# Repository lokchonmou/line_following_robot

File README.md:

line_following_robot
====================

line following robot with Arduino, using DFduino UNO, dfrobot motor, home_made IR sensor to track line

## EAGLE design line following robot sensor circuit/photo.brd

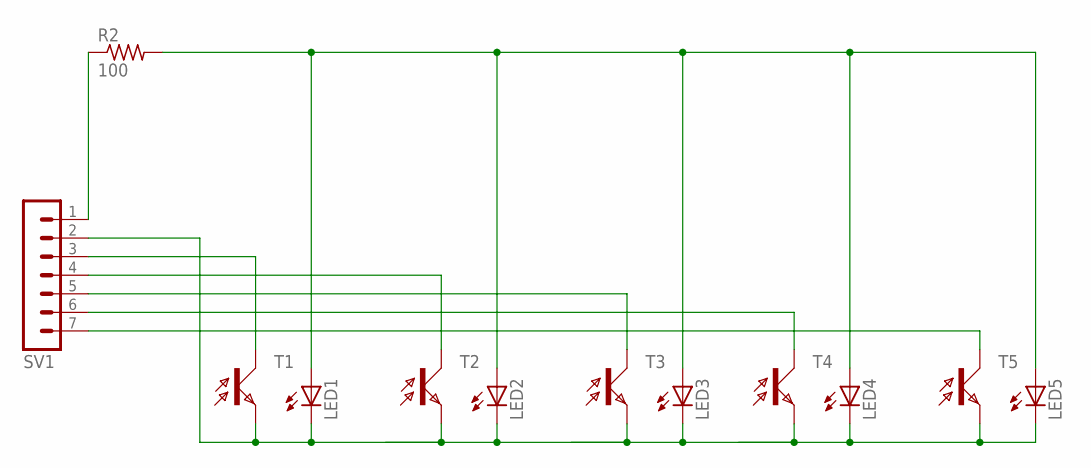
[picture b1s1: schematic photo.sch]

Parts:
LED1, LED2, LED3, LED4, LED5: LED3MM
R2: 100; 0204/7
SV1: MA07-1
T1, T2, T3, T4, T5: LPT80A

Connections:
unnamed: LED1.A, LED2.A, LED3.A, LED4.A, LED5.A, R2.2
unnamed: SV1.4, T2.C
unnamed: R2.1, SV1.1
unnamed: SV1.3, T1.C
unnamed: SV1.5, T3.C
unnamed: SV1.6, T4.C
unnamed: LED1.K (C), LED2.K (C), LED3.K (C), LED4.K (C), LED5.K (C), SV1.2, T1.E, T2.E, T3.E, T4.E, T5.E
unnamed: SV1.7, T5.C

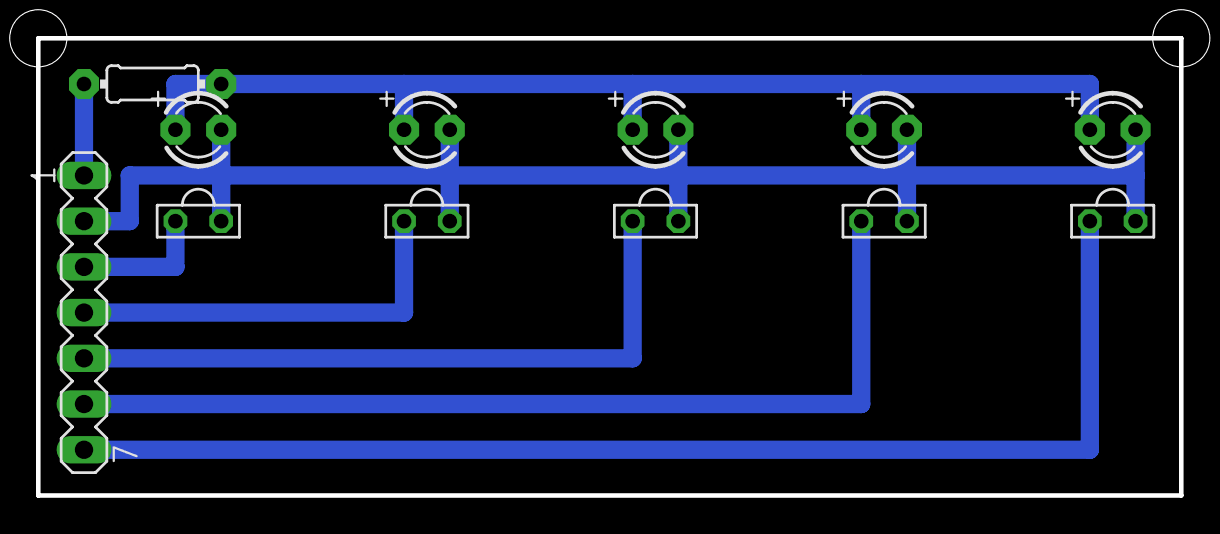
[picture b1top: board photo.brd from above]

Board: 2 copper layers, 63.5 x 25.4 mm, 12 parts (0 on the bottom side), 8 nets.

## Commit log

2014-06-11 version 1.0
    wt sensor board circuit, robot body scr file and pid controller code
2014-06-11 version 1.1
    加入3個step by step coding教學
2014-06-12 match version
    add a match version, using library and adding a RGB LED color sensor
2015-07-28 version 2.1
    1. Added a new LCD GUI to tune the Kp, Kd, easier to setup
    2. Added EEPROM library, can save the Kp, Kd data, not need to tune
    again when restarting(DON’T SAVE TOO MUCH, EEPROM only 100,000 cycle
    life)
    3. Change the edge sensor pin to digital pin, A4, A5 is used to IIC
    communication.
2015-07-28 version 2.2
    MENU:
    1. added black/white line option
    2. added tuning sample time option
    3. also, can save the above 2 data to EEPROM
2015-07-28 version 2.2
    1. bugs fixed
    2. new design to the car body, make it more stable
    This is the final version of 2015
2018-11-08 Add a line following simulator
